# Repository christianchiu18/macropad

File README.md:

This is the process of my macropad

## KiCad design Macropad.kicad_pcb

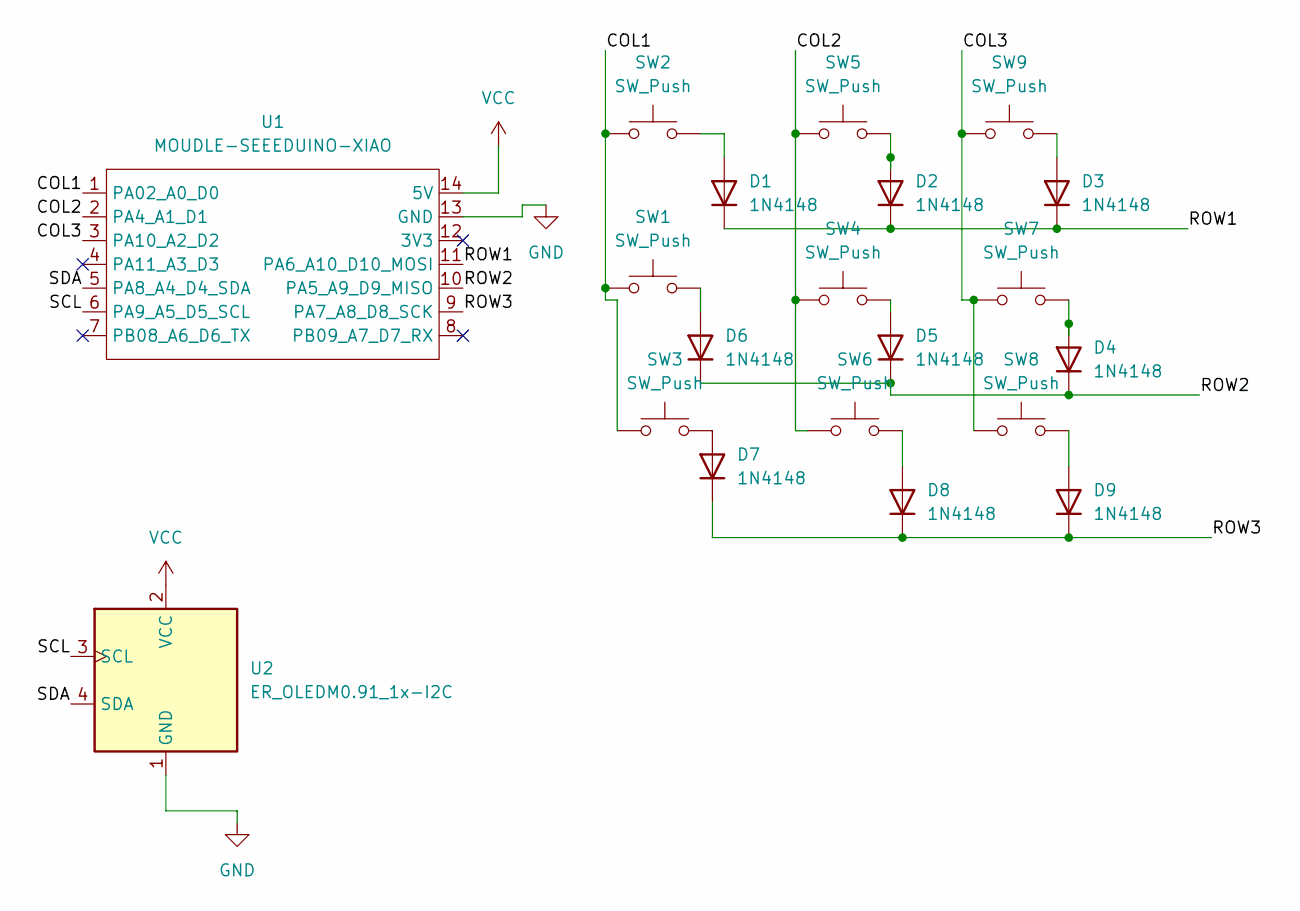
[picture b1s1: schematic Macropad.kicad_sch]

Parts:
D1, D2, D3, D4, D5, D6, D7, D8, D9: 1N4148; D_DO-35_SOD27_P7.62mm_Horizontal
SW1, SW2, SW3, SW4, SW5, SW6, SW7, SW8, SW9: SW_Push; SW_Cherry_MX_1.00u_PCB
U1: MOUDLE-SEEEDUINO-XIAO; XIAO-Generic-Hybrid-14P-2.54-21X17.8MM
U2: ER_OLEDM0.91_1x-I2C

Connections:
/COL1: SW1.1, SW2.1, SW3.1, U1.1 (PA02_A0_D0)
/COL2: SW4.1, SW5.1, SW6.1, U1.2 (PA4_A1_D1)
/COL3: SW7.1, SW8.1, SW9.1, U1.3 (PA10_A2_D2)
/ROW1: D1.1 (K), D2.1 (K), D3.1 (K), U1.11 (PA6_A10_D10_MOSI)
/ROW2: D4.1 (K), D5.1 (K), D6.1 (K), U1.10 (PA5_A9_D9_MISO)
/ROW3: D7.1 (K), D8.1 (K), D9.1 (K), U1.9 (PA7_A8_D8_SCK)
/SCL: U1.6 (PA9_A5_D5_SCL), U2.3 (SCL)
/SDA: U1.5 (PA8_A4_D4_SDA), U2.4 (SDA)
GND: U1.13 (GND), U2.1 (GND)
unnamed: D1.2 (A), SW2.2
unnamed: D2.2 (A), SW5.2
unnamed: D3.2 (A), SW9.2
unnamed: D4.2 (A), SW7.2
unnamed: D5.2 (A), SW4.2
unnamed: D6.2 (A), SW1.2
unnamed: D7.2 (A), SW3.2
unnamed: D8.2 (A), SW6.2
unnamed: D9.2 (A), SW8.2
VCC: U1.14 (5V), U2.2 (VCC)

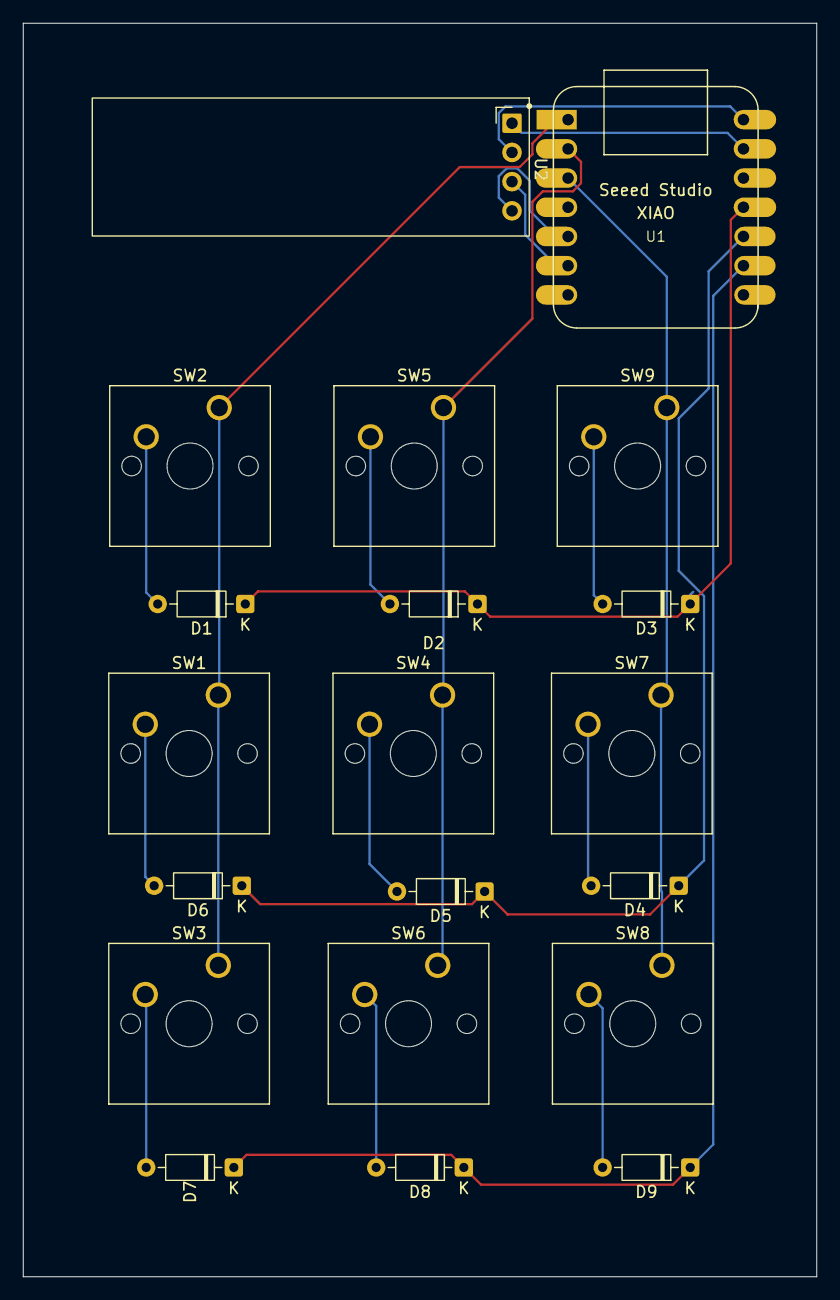
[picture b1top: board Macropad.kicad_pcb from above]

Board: 2 copper layers, 69.0 x 109.0 mm, 20 parts (0 on the bottom side), 19 nets.
